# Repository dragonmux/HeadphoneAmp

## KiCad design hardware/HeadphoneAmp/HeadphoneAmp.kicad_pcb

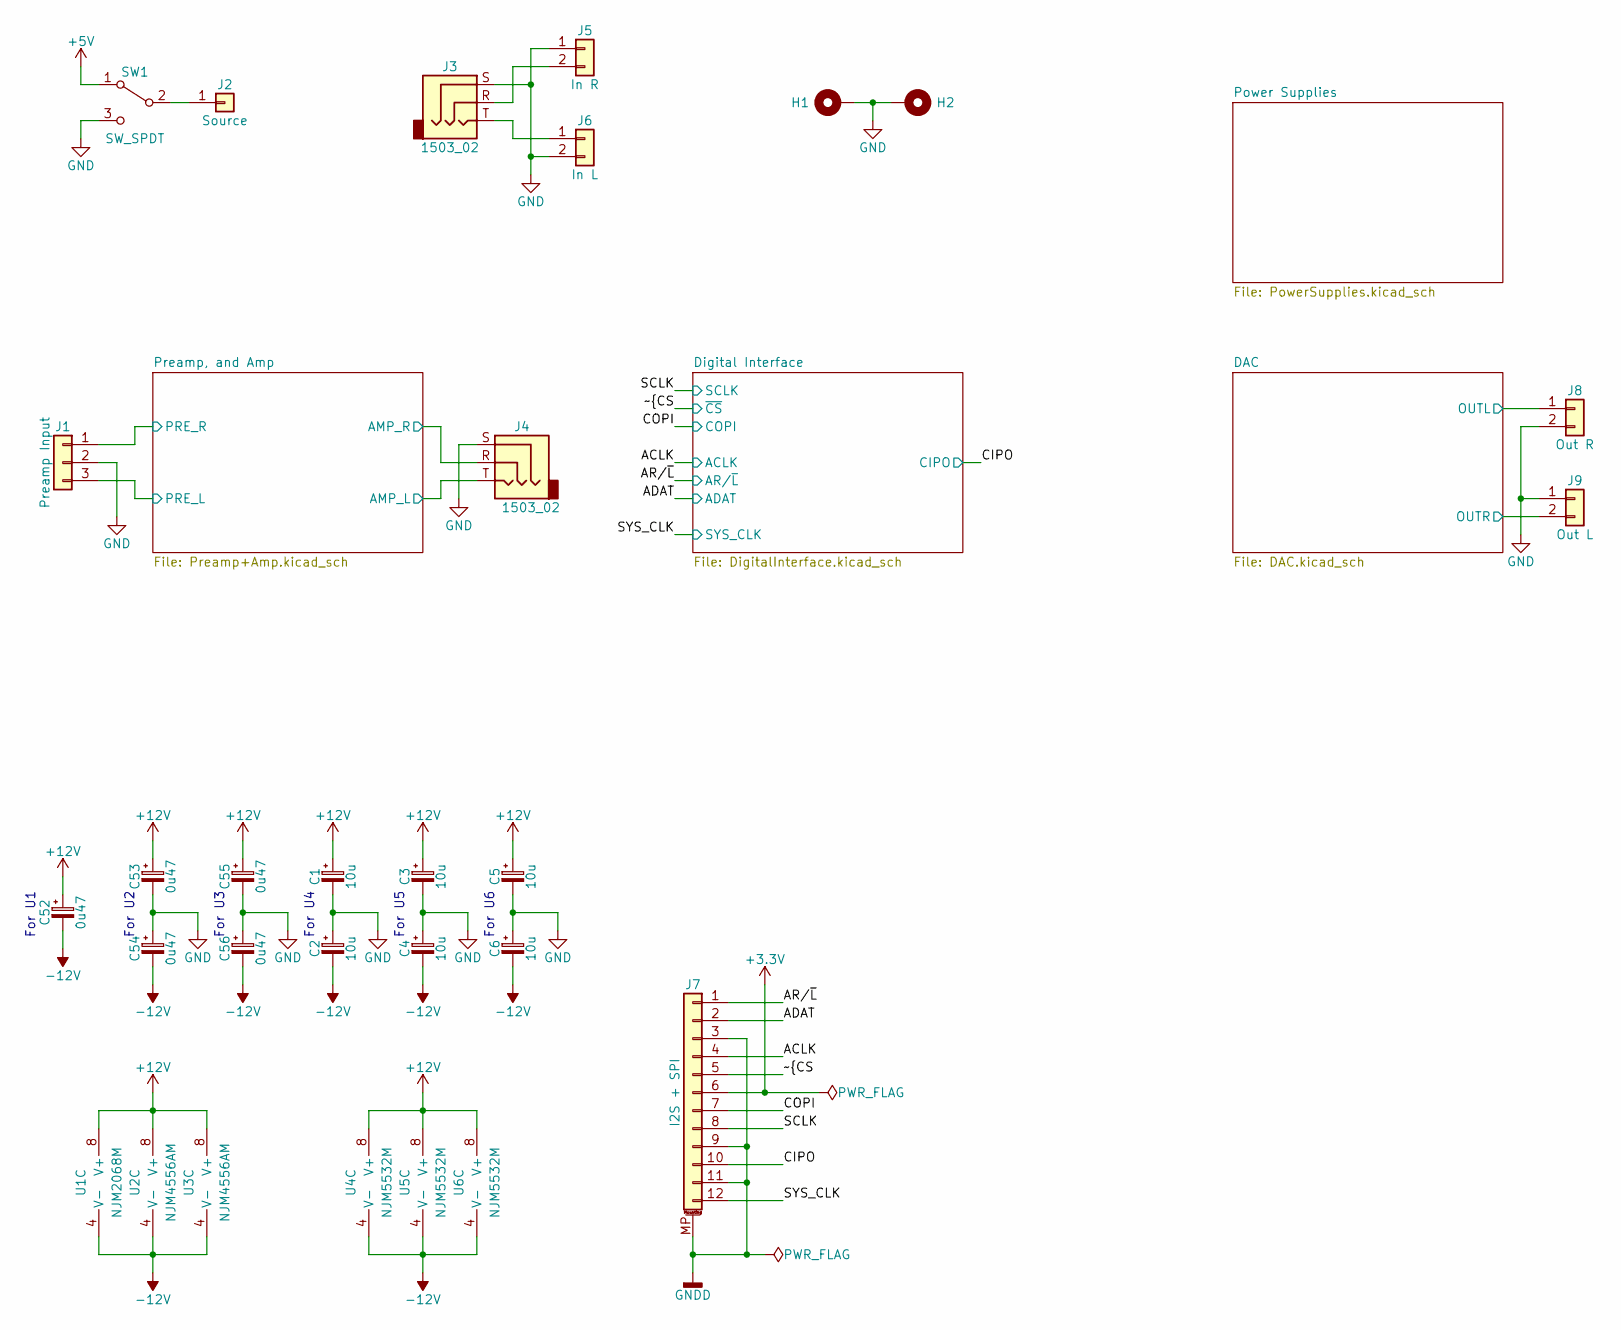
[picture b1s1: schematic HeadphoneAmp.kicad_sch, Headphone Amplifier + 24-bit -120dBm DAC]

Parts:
C1, C2, C3, C4, C5, C6: 10u; CP_EIA-3216-18_A; MPN 293D106X0016A2TE3
C52, C53, C54, C55, C56: 0u47; CP_EIA-3216-18_A; MPN F931V474KAA
H1, H2: MountingHole_Pad; MountingHole_3.2mm_M3_Pad
J1: Preamp Input; PinHeader_1x03_P2.54mm_Vertical
J2: Source; PinHeader_1x01_P2.54mm_Vertical
J3, J4: 1503_02; 1503-02; MPN 1503 02
J5: In R; PinHeader_1x02_P2.54mm_Vertical
J6: In L; PinHeader_1x02_P2.54mm_Vertical
J7: I2S + SPI; 1-17345952-2_1x12-1MP_P0.5mm_Horizontal; MPN 1-1734592-2
J8: Out R; PinHeader_1x02_P2.54mm_Vertical
J9: Out L; PinHeader_1x02_P2.54mm_Vertical
SW1: SW_SPDT; PN1x-30EQ; MPN PN12SHNA03QE
U1: NJM2068M; SO-8_5.3x5.3mm_P1.27mm; MPN NJM2068M
U2, U3: NJM4556AM; SO-8_5.3x5.3mm_P1.27mm; MPN NJM4556AM
U4, U5, U6: NJM5532M; SO-8_5.3x5.3mm_P1.27mm; MPN NJM5532M

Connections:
+3V3: J7.6; also elsewhere on the board
+5V: SW1.1 (A); also elsewhere on the board
+12V: C1.1, C3.1, C5.1, C52.1, C53.1, C55.1, U1.8 (V+), U2.8 (V+), U3.8 (V+), U4.8 (V+), U5.8 (V+), U6.8 (V+); also elsewhere on the board
-12V: C2.2, C4.2, C6.2, C52.2, C54.2, C56.2, U1.4 (V-), U2.4 (V-), U3.4 (V-), U4.4 (V-), U5.4 (V-), U6.4 (V-); also elsewhere on the board
/ACLK: J7.4; also elsewhere on the board
/ADAT: J7.2; also elsewhere on the board
/AR/~L: J7.1; also elsewhere on the board
/CIPO: J7.10; also elsewhere on the board
/COPI: J7.7; also elsewhere on the board
/DAC/OUTL: J8.1; also elsewhere on the board
/DAC/OUTR: J9.2; also elsewhere on the board
/Preamp, and Amp/AMP_L: J4.T; also elsewhere on the board
/Preamp, and Amp/AMP_R: J4.R; also elsewhere on the board
/Preamp, and Amp/PRE_L: J1.3; also elsewhere on the board
/Preamp, and Amp/PRE_R: J1.1; also elsewhere on the board
/SCLK: J7.8; also elsewhere on the board
/SYS_CLK: J7.12; also elsewhere on the board
/~CS: J7.5; also elsewhere on the board
GND: C1.2, C2.1, C3.2, C4.1, C5.2, C6.1, C53.2, C54.1, C55.2, C56.1, H1.1, H2.1, J1.2, J3.S, J4.S, J5.1, J6.2, J8.2, J9.1, SW1.3 (C); also elsewhere on the board
GNDD: J7.3, J7.9, J7.11, J7.MP (MountPin); also elsewhere on the board
unnamed: J2.1, SW1.2 (B)
unnamed: J3.R, J5.2
unnamed: J3.T, J6.1

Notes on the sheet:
For U4
For U6
For U3
For U1
For U5
For U2

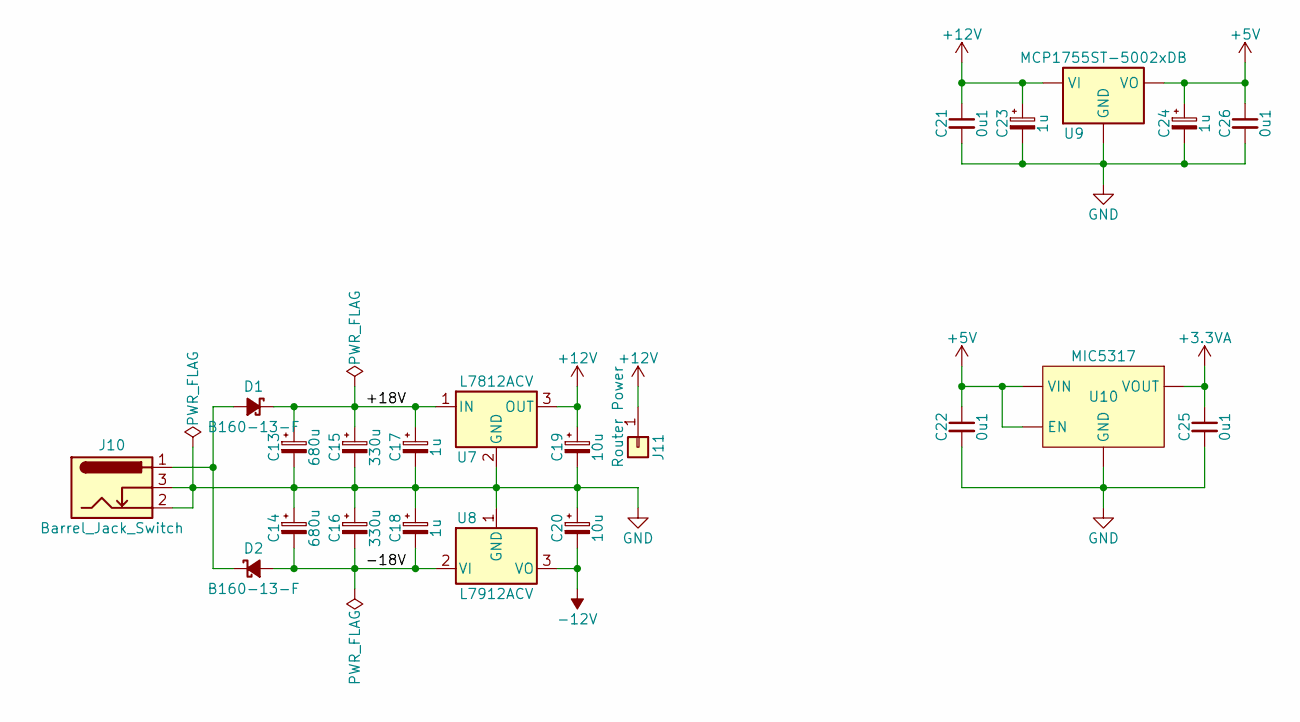
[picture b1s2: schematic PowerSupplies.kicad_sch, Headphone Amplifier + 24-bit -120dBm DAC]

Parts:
C13, C14: 680u; CP_Radial_D10.0mm_P5.00mm; MPN 25PX680MEFC10X12.5
C15, C16: 330u; CP_Radial_D8.0mm_P3.50mm; MPN 25PX330MEFC8X11.5
C17, C18: 1u; CP_EIA-3216-18_A; MPN 293D105X9025A2TE3
C19, C20: 10u; CP_EIA-3216-18_A; MPN 293D106X0016A2TE3
C21, C22, C26: 0u1; C1210; MPN ECH-U1C104GX5
C23, C24: 1u; CP_EIA-3216-18_A; MPN 293D105X9016A2TE3
C25: 0u1; C0603; MPN CGA3E2X7R1E104K080AA
D1, D2: B160-13-F; D_SMA; MPN B160-13-F
J10: Barrel_Jack_Switch; BarrelJack_GCT_DCJ200-10-A_Horizontal; MPN DCJ200-10-A-K1-K
J11: Router Power; PinHeader_1x01_P2.54mm_Vertical
U7: L7812ACV; TO-220-3_Vertical; MPN L7812ACV
U8: L7912ACV; TO-220-3_Vertical; MPN L7912ACV
U9: MCP1755ST-5002xDB; SOT-223; MPN MCP1755ST-5002E/DB
U10: MIC5317; SOT-23-5; MPN MIC5317-3.3YM5-TR

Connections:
+3.3VA: C25.1, U10.5 (VOUT); also elsewhere on the board
+5V: C22.1, C24.1, C26.1, U9.3 (VO), U10.1 (VIN), U10.3 (EN); also elsewhere on the board
+12V: C19.1, C21.1, C23.1, J11.1, U7.3 (OUT), U9.1 (VI); also elsewhere on the board
-12V: C20.2, U8.3 (VO); also elsewhere on the board
/Power Supplies/+18V: C13.1, C15.1, C17.1, D1.1 (K), U7.1 (IN)
/Power Supplies/-18V: C14.2, C16.2, C18.2, D2.2 (A), U8.2 (VI)
GND: C13.2, C14.1, C15.2, C16.1, C17.2, C18.1, C19.2, C20.1, C21.2, C22.2, C23.2, C24.2, C25.2, C26.2, J10.2, J10.3, U7.2 (GND), U8.1 (GND), U9.2 (GND), U10.2 (GND); also elsewhere on the board
unnamed: D1.2 (A), D2.1 (K), J10.1

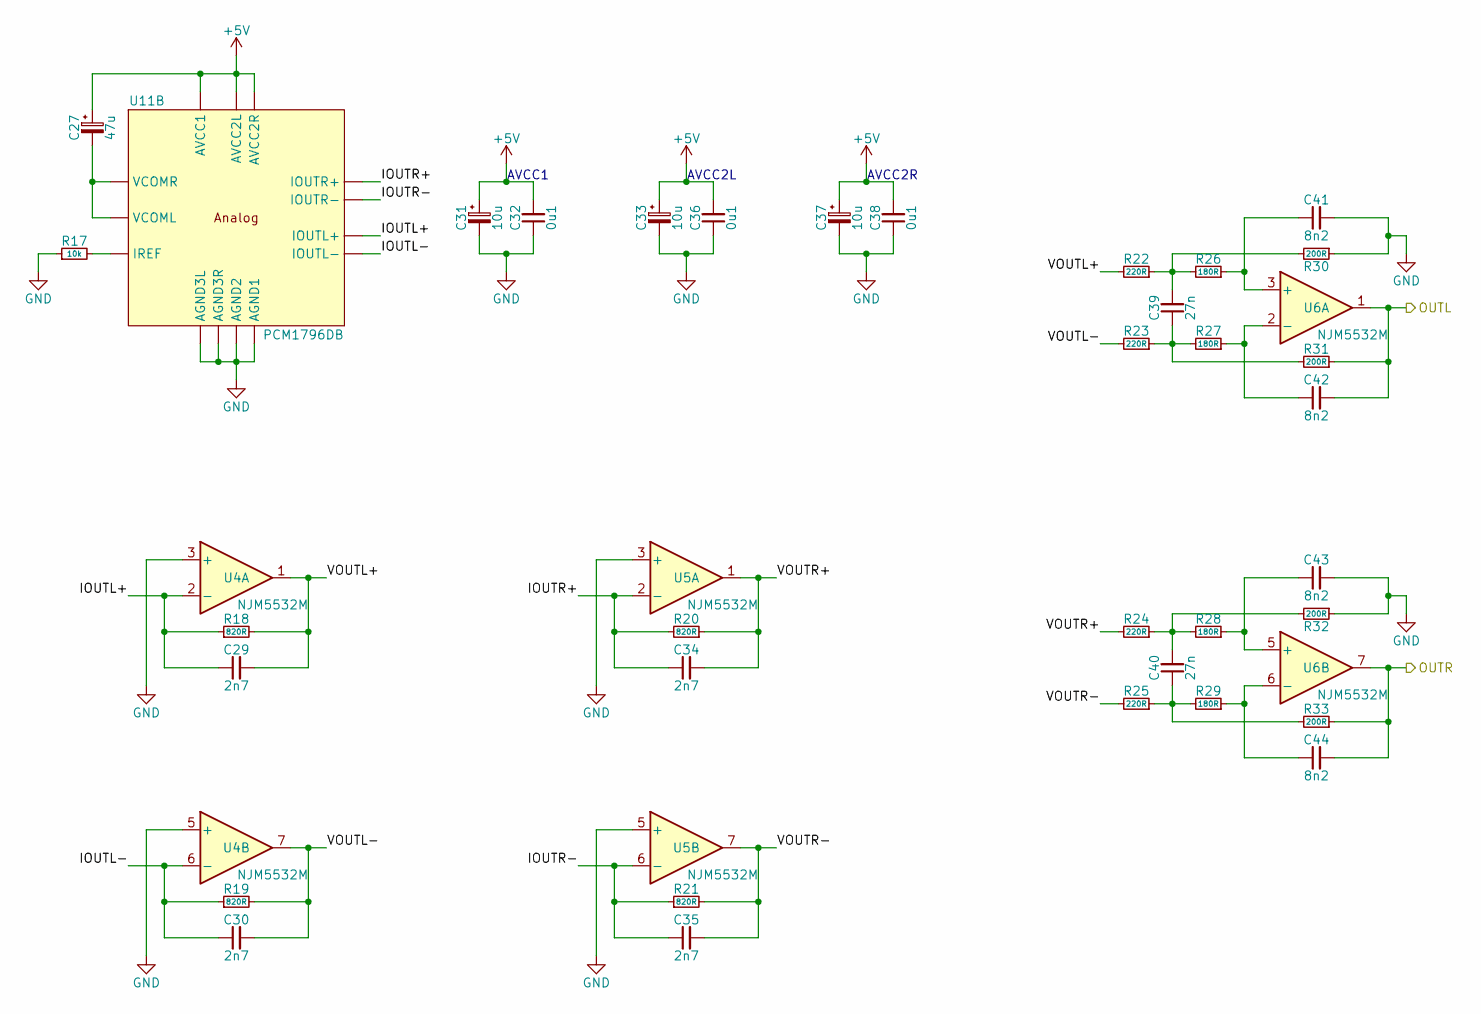
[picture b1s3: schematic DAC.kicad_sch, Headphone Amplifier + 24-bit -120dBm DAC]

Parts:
C27: 47u; CP_EIA-3528-21_B; MPN 293D476X9010B2TE3
C29, C30, C34, C35: 2n7; C0603; MPN ECH-U1C272GX5
C31, C33, C37: 10u; CP_EIA-3216-18_A; MPN 293D106X0016A2TE3
C32, C36, C38: 0u1; C1210; MPN ECH-U1C104GX5
C39, C40: 27n; C1206; MPN ECH-U1C273GX5
C41, C42, C43, C44: 8n2; C0805; MPN ECH-U1C822GX5
R17: 10k; R0603; MPN RN73H1JTTD1002B25
R18, R19, R20, R21: 820R; R0603; MPN RN73H1JTTD8200F100
R22, R23, R24, R25: 220R; R0603; MPN RN73H1JTTD2200F100
R26, R27, R28, R29: 180R; R0603; MPN RN73H1JTTD1800F100
R30, R31, R32, R33: 200R; R0603; MPN RN73H1JTTD2000B25
U4, U5, U6: NJM5532M; SO-8_5.3x5.3mm_P1.27mm; MPN NJM5532M
U11: PCM1796DB; SSOP-28_5.3x10.2mm_P0.65mm; MPN PCM1796DB

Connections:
+5V: C27.1, C31.1, C32.2, C33.1, C36.2, C37.1, C38.2, U11.15 (AVCC2R), U11.23 (AVCC1), U11.28 (AVCC2L); also elsewhere on the board
/DAC/IOUTL+: C29.1, R18.1, U4.2 (-), U11.25 (IOUTL+)
/DAC/IOUTL-: C30.1, R19.1, U4.6 (-), U11.26 (IOUTL-)
/DAC/IOUTR+: C34.1, R20.2, U5.2 (-), U11.17 (IOUTR+)
/DAC/IOUTR-: C35.1, R21.1, U5.6 (-), U11.18 (IOUTR-)
/DAC/OUTL: C42.2, R31.1, U6.1; also elsewhere on the board
/DAC/OUTR: C44.2, R33.1, U6.7; also elsewhere on the board
/DAC/VOUTL+: C29.2, R18.2, R22.2, U4.1
/DAC/VOUTL-: C30.2, R19.2, R23.2, U4.7
/DAC/VOUTR+: C34.2, R20.1, R24.2, U5.1
/DAC/VOUTR-: C35.2, R21.2, R25.2, U5.7
GND: C31.2, C32.1, C33.2, C36.1, C37.2, C38.1, C41.2, C43.2, R17.1, R30.1, R32.1, U4.3 (+), U4.5 (+), U5.3 (+), U5.5 (+), U11.16 (AGND3R), U11.19 (AGND1), U11.24 (AGND2), U11.27 (AGND3L); also elsewhere on the board
unnamed: C27.2, U11.21 (VCOMR), U11.22 (VCOML)
unnamed: C39.1, R23.1, R27.2, R31.2
unnamed: C39.2, R22.1, R26.2, R30.2
unnamed: C40.1, R25.1, R29.2, R33.2
unnamed: C40.2, R24.1, R28.2, R32.2
unnamed: C41.1, R26.1, U6.3 (+)
unnamed: C42.1, R27.1, U6.2 (-)
unnamed: C43.1, R28.1, U6.5 (+)
unnamed: C44.1, R29.1, U6.6 (-)
unnamed: R17.2, U11.20 (IREF)

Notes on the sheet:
AVCC2R
AVCC1
AVCC2L

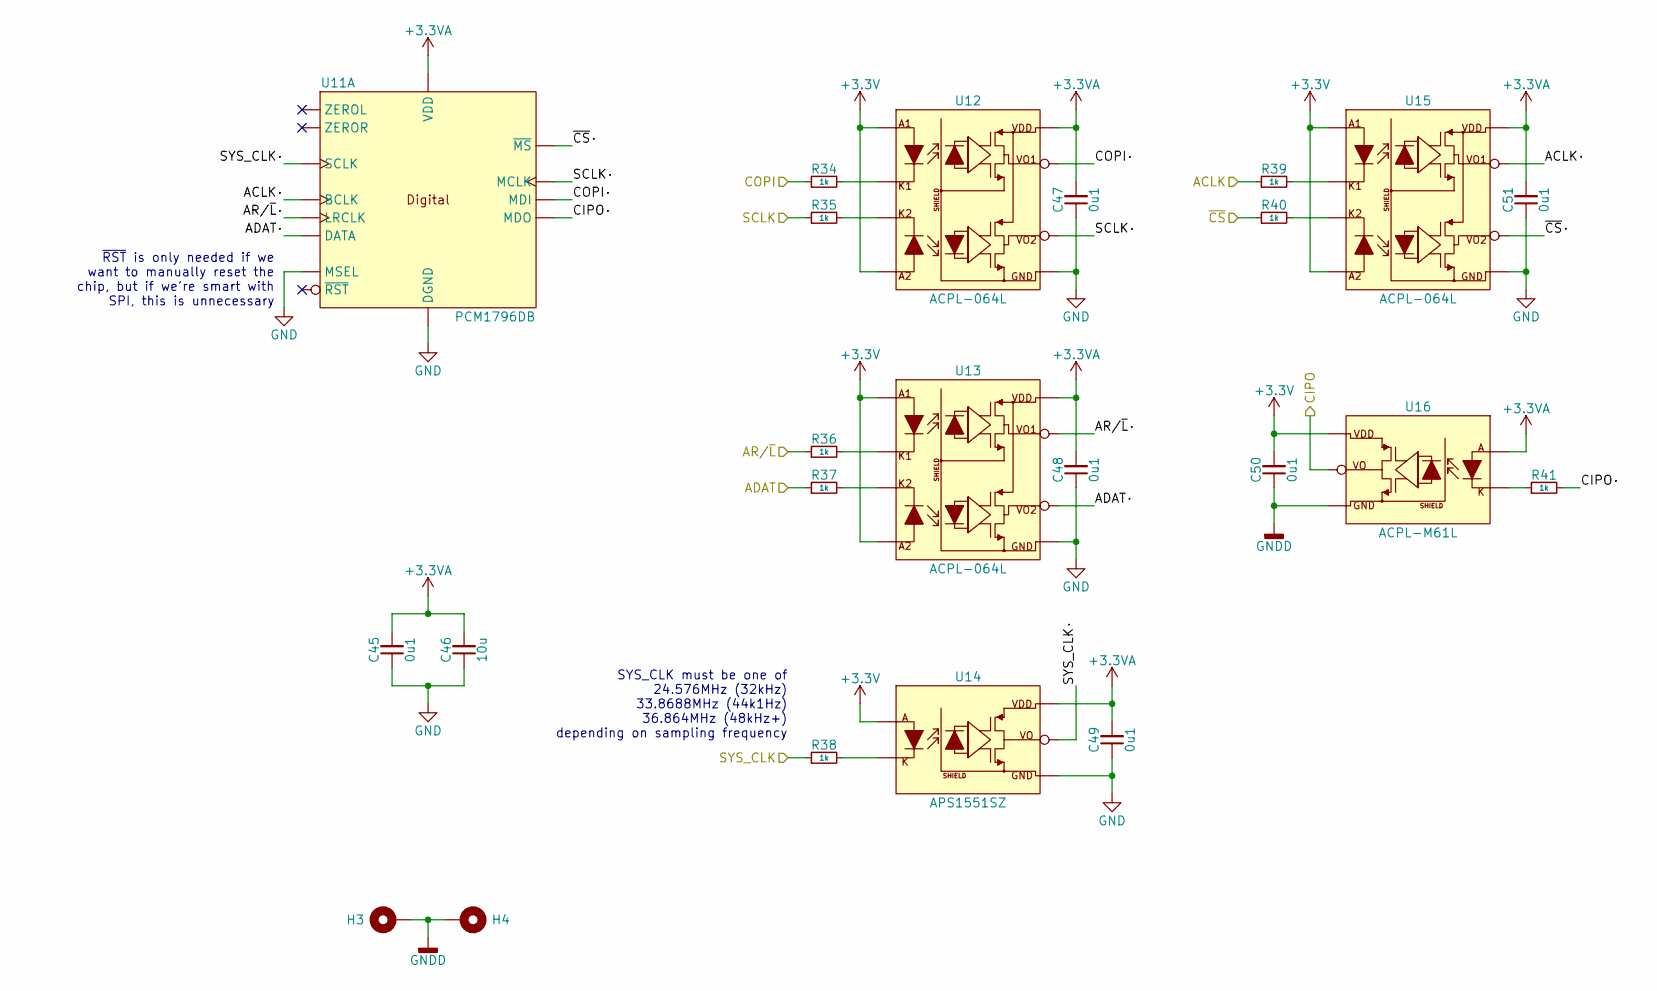
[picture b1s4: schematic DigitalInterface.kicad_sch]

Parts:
C45, C47, C48, C49, C50, C51: 0u1; C0603; MPN CGA3E2X7R1E104K080AA
C46: 10u; C0805; MPN GRM21BR61E106KA73L
H3, H4: MountingHole_Pad; MountingHole_3.2mm_M3_Pad
R34, R35, R36, R37, R38, R39, R40, R41: 1k; R0603; MPN CRCW06031K00FKEA
U11: PCM1796DB; SSOP-28_5.3x10.2mm_P0.65mm; MPN PCM1796DB
U12, U13, U15: ACPL-064L; SO-8_3.9x4.9mm_P1.27mm; MPN ACPL-064L-500E
U14: APS1551SZ; SO-5_4.4x4.3mm_P1.27mm; MPN APS1551SZ
U16: ACPL-M61L; SO-5_4.4x3.6mm_P1.27mm; MPN ACPL-M61L-5x0E

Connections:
+3.3VA: C45.2, C46.2, C47.2, C48.2, C49.2, C51.2, U11.9 (VDD), U12.8 (VDD), U13.8 (VDD), U14.6 (VDD), U15.8 (VDD), U16.1 (A); also elsewhere on the board
+3V3: C50.2, U12.1 (A1), U12.4 (A2), U13.1 (A1), U13.4 (A2), U14.1 (A), U15.1 (A1), U15.4 (A2), U16.6 (VDD); also elsewhere on the board
/ACLK: R39.1; also elsewhere on the board
/ADAT: R37.1; also elsewhere on the board
/AR/~L: R36.1; also elsewhere on the board
/CIPO: U16.5 (VO); also elsewhere on the board
/COPI: R34.1; also elsewhere on the board
/Digital Interface/ACLK·: U11.6 (BCLK), U15.7 (VO1)
/Digital Interface/ADAT·: U11.5 (DATA), U13.6 (VO2)
/Digital Interface/AR/~L·: U11.4 (LRCLK), U13.7 (VO1)
/Digital Interface/CIPO·: R41.2, U11.13 (MDO)
/Digital Interface/COPI·: U11.11 (MDI), U12.7 (VO1)
/Digital Interface/SCLK·: U11.12 (MCLK), U12.6 (VO2)
/Digital Interface/SYS_CLK·: U11.7 (SCLK), U14.5 (VO)
/Digital Interface/~CS·: U11.10 (~MS), U15.6 (VO2)
/SCLK: R35.1; also elsewhere on the board
/SYS_CLK: R38.1; also elsewhere on the board
/~CS: R40.1; also elsewhere on the board
GND: C45.1, C46.1, C47.1, C48.1, C49.1, C51.1, U11.3 (MSEL), U11.8 (DGND), U12.5 (GND), U13.5 (GND), U14.4 (GND), U15.5 (GND); also elsewhere on the board
GNDD: C50.1, H3.1, H4.1, U16.4 (GND); also elsewhere on the board
unnamed: R34.2, U12.2 (K1)
unnamed: R35.2, U12.3 (K2)
unnamed: R36.2, U13.2 (K1)
unnamed: R37.2, U13.3 (K2)
unnamed: R38.2, U14.3 (K)
unnamed: R39.2, U15.2 (K1)
unnamed: R40.2, U15.3 (K2)
unnamed: R41.1, U16.3 (K)

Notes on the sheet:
SYS_CLK must be one of 24.576MHz (32kHz) 33.8688MHz (44k1Hz) 36.864MHz (48kHz+) depending on sampling frequency
~{RST} is only needed if we want to manually reset the chip, but if we're smart with SPI, this is unnecessary

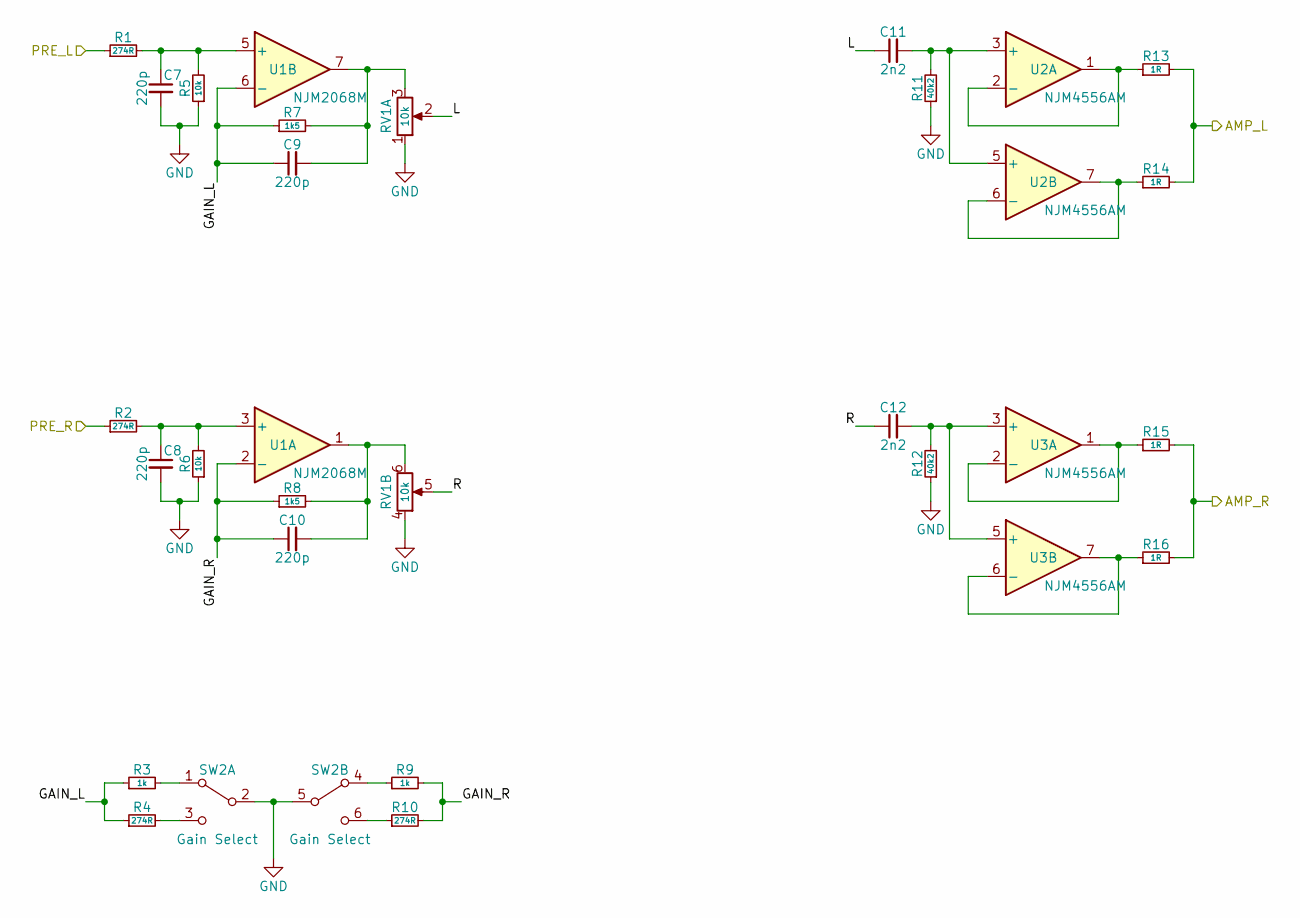
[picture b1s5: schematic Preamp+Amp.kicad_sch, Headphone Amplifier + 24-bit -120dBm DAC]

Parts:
C7, C8, C9, C10: 220p; C0603; MPN ECH-U1C221GX5
C11, C12: 2n2; C0603; MPN ECH-U1C222GX5
R1, R2, R4, R10: 274R; R0603; MPN RN731JTTD2740B25
R3, R9: 1k; R0603; MPN RN73H1JTTD1001D25
R5, R6: 10k; R0603; MPN RN73H1JTTD1002B25
R7, R8: 1k5; R0603; MPN RN73H1JTTD1501B25
R11, R12: 40k2; R0603; MPN RN73H1ETTP4022F25
R13, R14, R15, R16: 1R; R1206; MPN MCA12060C1008FP500
RV1: 10k; PTD902; MPN PTD902-2015F-A103
SW2: Gain Select; PN2x-30EQ; MPN PN22LENA03QE
U1: NJM2068M; SO-8_5.3x5.3mm_P1.27mm; MPN NJM2068M
U2, U3: NJM4556AM; SO-8_5.3x5.3mm_P1.27mm; MPN NJM4556AM

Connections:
/Preamp, and Amp/AMP_L: R13.2, R14.2; also elsewhere on the board
/Preamp, and Amp/AMP_R: R15.2, R16.2; also elsewhere on the board
/Preamp, and Amp/GAIN_L: C9.1, R3.1, R4.1, R7.1, U1.6 (-)
/Preamp, and Amp/GAIN_R: C10.1, R8.1, R9.2, R10.2, U1.2 (-)
/Preamp, and Amp/L: C11.1, RV1.2
/Preamp, and Amp/PRE_L: R1.1; also elsewhere on the board
/Preamp, and Amp/PRE_R: R2.1; also elsewhere on the board
/Preamp, and Amp/R: C12.1, RV1.5
GND: C7.2, C8.2, R5.1, R6.1, R11.1, R12.1, RV1.1, RV1.4, SW2.2 (B), SW2.5 (B); also elsewhere on the board
unnamed: C7.1, R1.2, R5.2, U1.5 (+)
unnamed: C8.1, R2.2, R6.2, U1.3 (+)
unnamed: C9.2, R7.2, RV1.3, U1.7
unnamed: C10.2, R8.2, RV1.6, U1.1
unnamed: C11.2, R11.2, U2.3 (+), U2.5 (+)
unnamed: C12.2, R12.2, U3.3 (+), U3.5 (+)
unnamed: R3.2, SW2.1 (A)
unnamed: R4.2, SW2.3 (C)
unnamed: R9.1, SW2.4 (A)
unnamed: R10.1, SW2.6 (C)
unnamed: R13.1, U2.1, U2.2 (-)
unnamed: R14.1, U2.6 (-), U2.7
unnamed: R15.1, U3.1, U3.2 (-)
unnamed: R16.1, U3.6 (-), U3.7

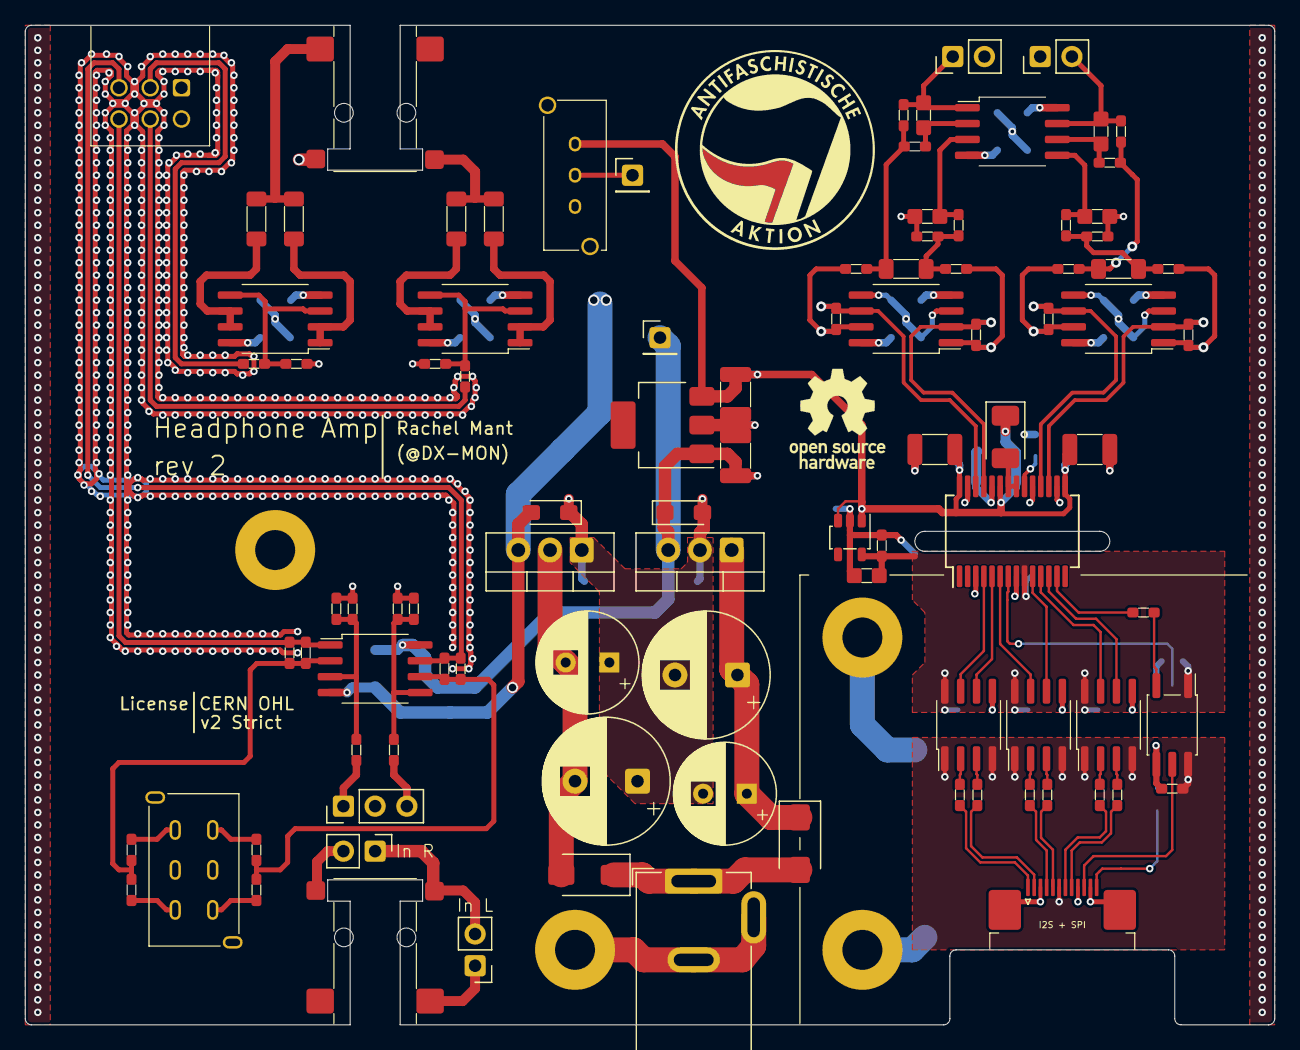
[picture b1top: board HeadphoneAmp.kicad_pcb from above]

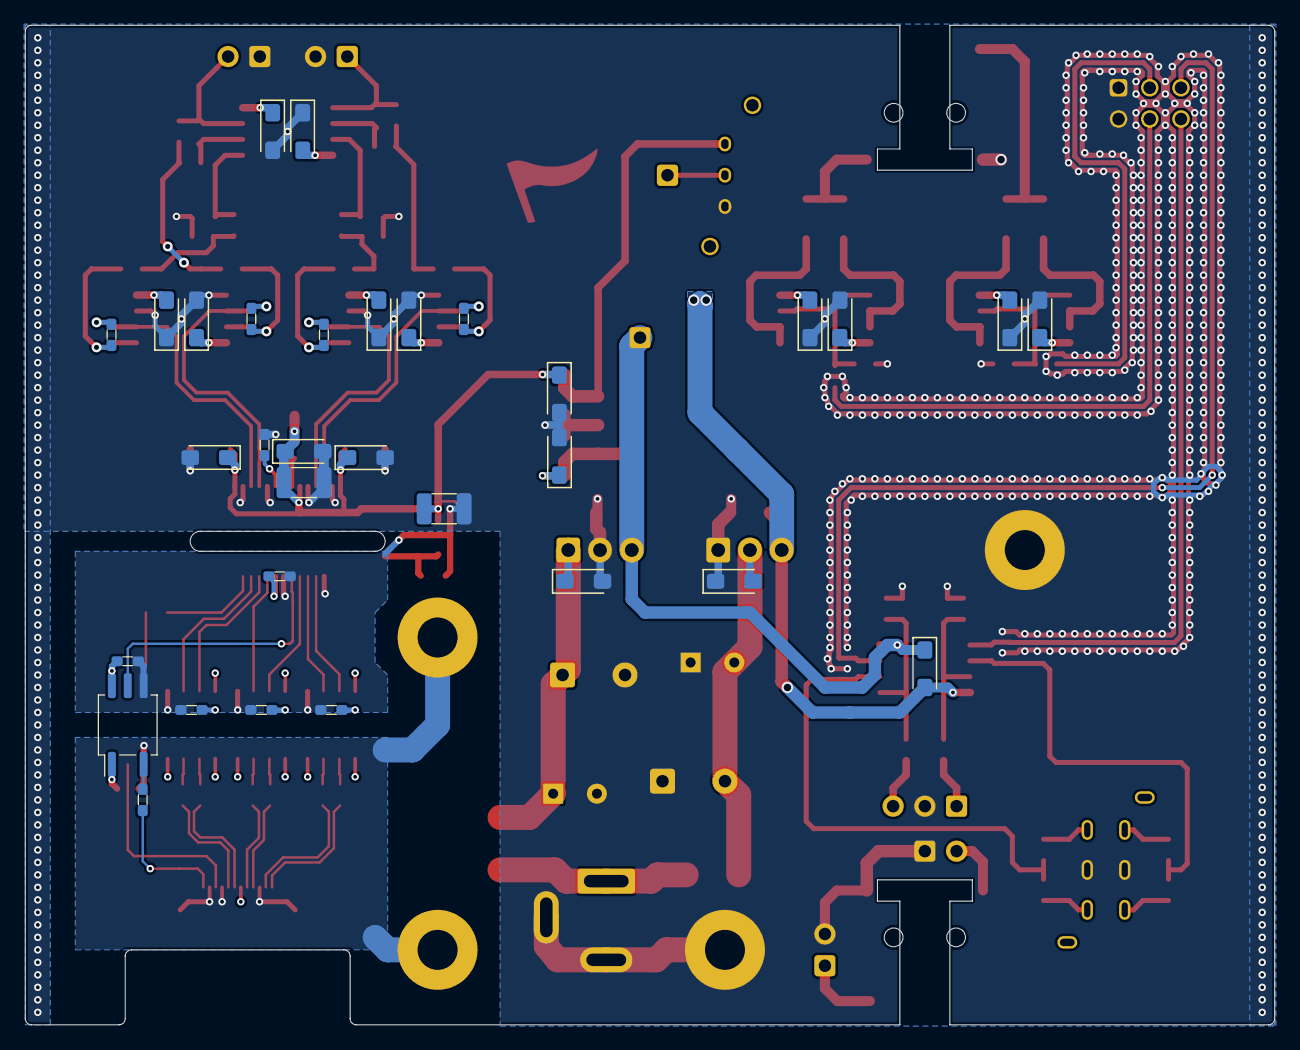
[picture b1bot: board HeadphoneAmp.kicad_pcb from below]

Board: 4 copper layers, 100.0 x 80.0 mm, 134 parts (32 on the bottom side), 79 nets.

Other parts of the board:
G1: ANTIFA; Antifaschistische-Aktion_Inv_600dpi
G2: OSHW-Logo_7.5x8mm_SilkScreen

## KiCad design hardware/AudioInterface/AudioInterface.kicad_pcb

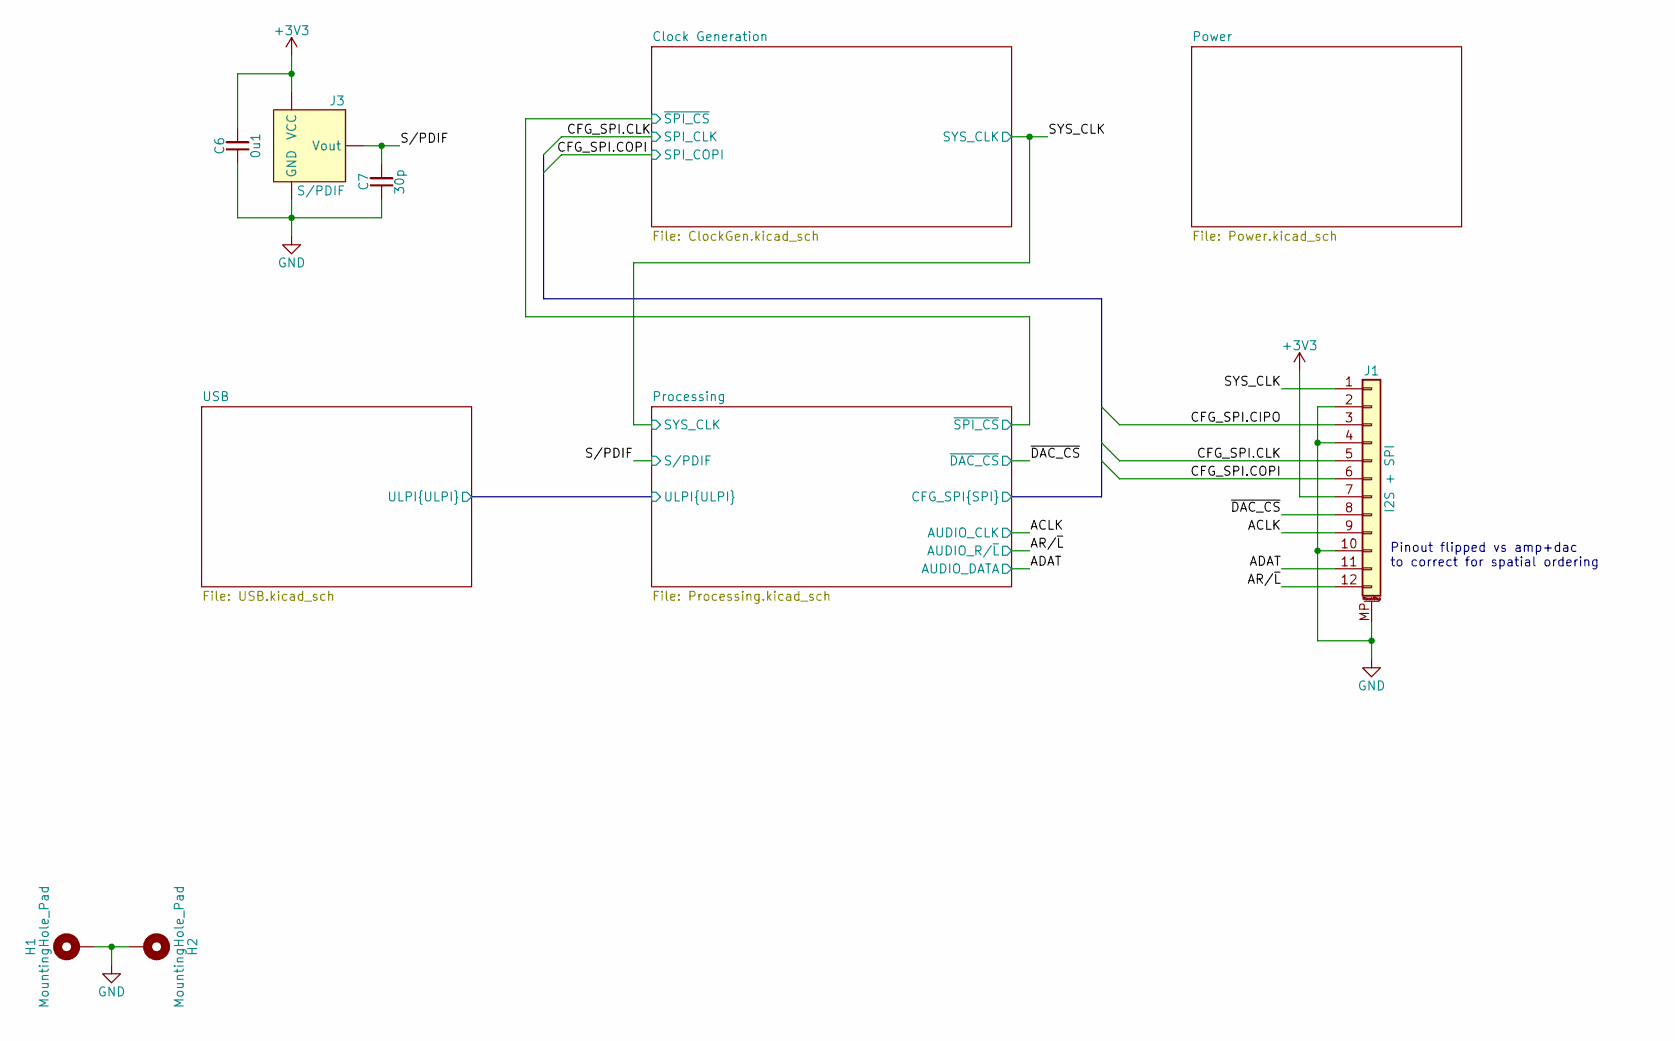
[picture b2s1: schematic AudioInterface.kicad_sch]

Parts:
C6: 0u1; C0603; MPN CGA3E2X7R1E104K080AA
C7: 30p; C0603; MPN CC0603FRNPO9BN300
H1, H2: MountingHole_Pad; MountingHole_3.2mm_M3_Pad
J1: I2S + SPI; 1-17345952-2_1x12-1MP_P0.5mm_Horizontal; MPN 1-1734592-2
J3: S/PDIF; S-PDIF_Receiver; MPN FCR684208R

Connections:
+3V3: C6.2, J1.7, J3.3 (VCC); also elsewhere on the board
/ACLK: J1.9; also elsewhere on the board
/ADAT: J1.11; also elsewhere on the board
/AR/~L: J1.12; also elsewhere on the board
/Processing/CFG_SPI.CIPO: J1.3; also elsewhere on the board
/Processing/CFG_SPI.CLK: J1.5; also elsewhere on the board
/Processing/CFG_SPI.COPI: J1.6; also elsewhere on the board
/SYS_CLK: J1.1; also elsewhere on the board
/S/PDIF: C7.2, J3.1 (Vout); also elsewhere on the board
/~DAC_CS: J1.8; also elsewhere on the board
DGND: C6.1, C7.1, H1.1, H2.1, J1.2, J1.4, J1.10, J1.MP (MountPin), J3.2 (GND); also elsewhere on the board

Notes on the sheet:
Pinout flipped vs amp+dac to correct for spatial ordering

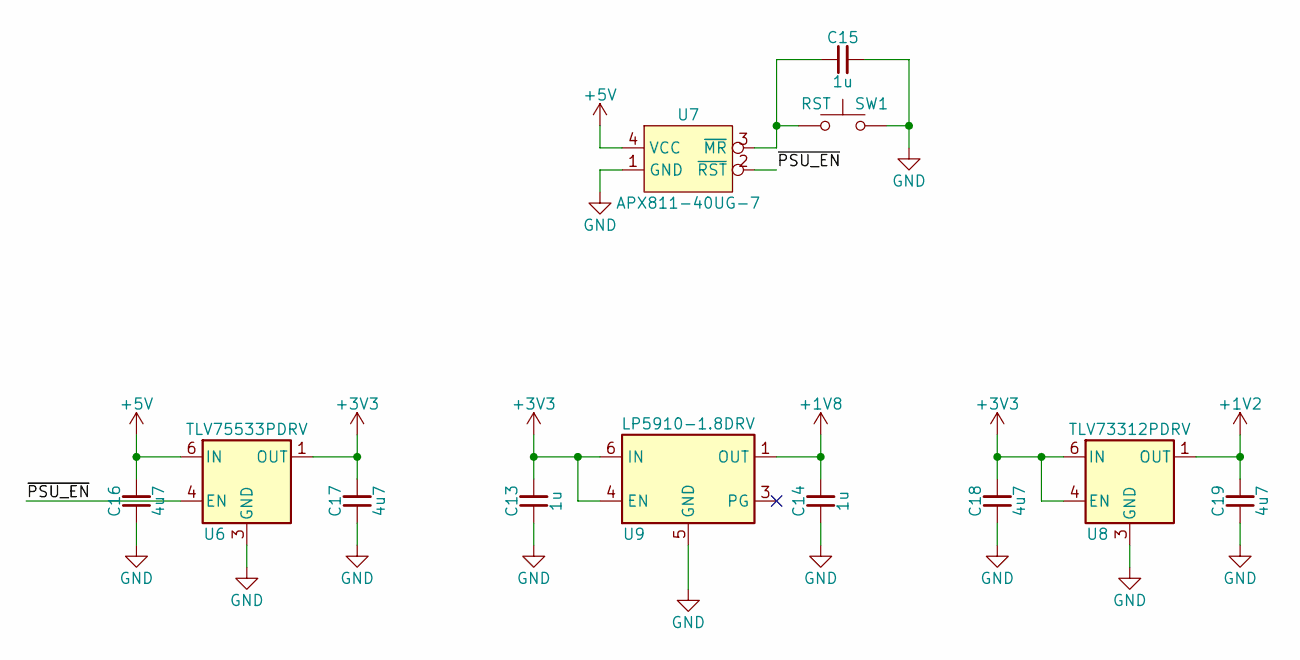
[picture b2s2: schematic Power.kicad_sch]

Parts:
C13, C14, C15: 1u; C0603; MPN C0603C105K4RAC7867
C16, C17, C18, C19: 4u7; C0603; MPN C1608X5R1C475K080AC
SW1: RST; B3U-1000P-B; MPN B3U-1000P-B
U6: TLV75533PDRV; WSON-6-1EP_2x2mm_P0.65mm_EP1x1.6mm; MPN TLV75533PDRVR
U7: APX811-40UG-7; SOT-143; MPN APX811-40UG-7
U8: TLV73312PDRV; WSON-6-1EP_2x2mm_P0.65mm_EP1x1.6mm; MPN TLV73312PQDRVRQ1
U9: LP5910-1.8DRV; WSON-6-1EP_2x2mm_P0.65mm_EP1x1.6mm; MPN LP5910-1.8DRVR

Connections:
+1V2: C19.2, U8.1 (OUT); also elsewhere on the board
+1V8: C14.2, U9.1 (OUT); also elsewhere on the board
+3V3: C13.2, C17.2, C18.2, U6.1 (OUT), U8.4 (EN), U8.6 (IN), U9.4 (EN), U9.6 (IN); also elsewhere on the board
+5V: C16.2, U6.6 (IN), U7.4 (VCC); also elsewhere on the board
/Power/~PSU_EN: U6.4 (EN), U7.2 (~RST)
DGND: C13.1, C14.1, C15.2, C16.1, C17.1, C18.1, C19.1, SW1.2, U6.2 (NC), U6.3 (GND), U6.5 (NC), U6.7 (GND), U7.1 (GND), U8.2 (NC), U8.3 (GND), U8.5 (NC), U8.7 (GND), U9.2 (NC), U9.5 (GND), U9.7 (EP); also elsewhere on the board
unnamed: C15.1, SW1.1, U7.3 (~MR)

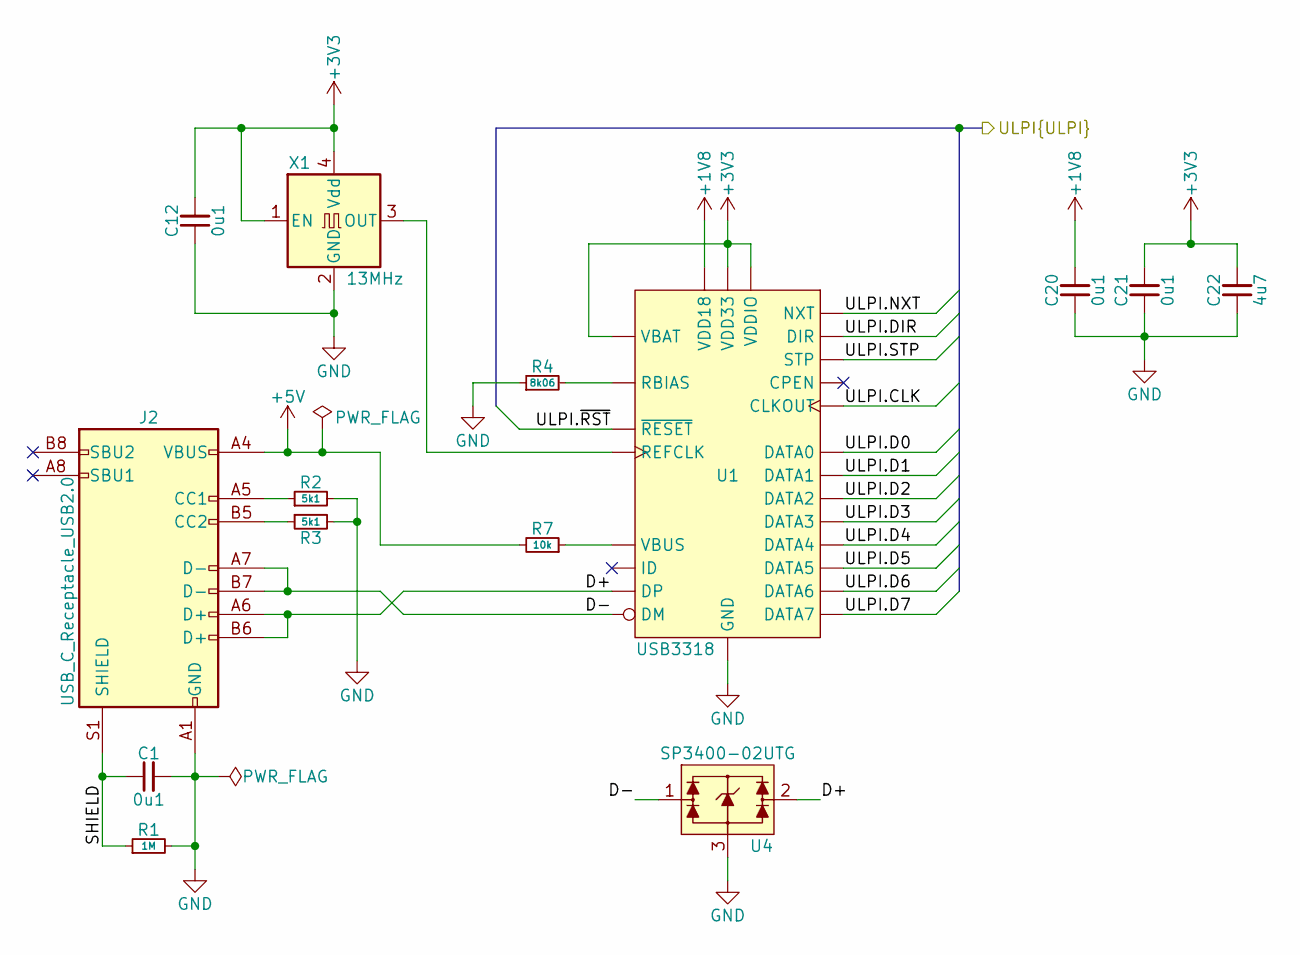
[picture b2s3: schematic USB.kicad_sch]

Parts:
C1, C12, C20, C21: 0u1; C0603; MPN CGA3E2X7R1E104K080AA
C22: 4u7; C0603; MPN C1608X5R1C475K080AC
J2: USB_C_Receptacle_USB2.0; USB_C_Receptacle_HRO_TYPE-C-31-M-12; MPN TYPE-C-31-M-12
R1: 1M; R0603; MPN CRCW06031M00FKEA
R2, R3: 5k1; R0603; MPN CRCW06035K10FKEA
R4: 8k06; R0603; MPN CRCW06038K06FKEA
R7: 10k; R0603; MPN CRCW060310K0FKEA
U1: USB3318; QFN-24-1EP_4x4mm_P0.5mm_EP2.6x2.6mm; MPN USB3318-CP-TR
U4: SP3400-02UTG; UDFN-6L; MPN SP3400-02UTG
X1: 13MHz; SMD2520; MPN 8W-13.000MBE-T

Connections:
+1V8: C20.2, U1.21 (VDD18); also elsewhere on the board
+3V3: C12.2, C21.2, C22.2, U1.3 (VBAT), U1.4 (VDD33), U1.17 (VDDIO), X1.1 (EN), X1.4 (Vdd); also elsewhere on the board
+5V: J2.A4 (VBUS), J2.A9 (VBUS), J2.B4 (VBUS), J2.B9 (VBUS), R7.2; also elsewhere on the board
/Processing/ULPI.CLK: U1.12 (CLKOUT); also elsewhere on the board
/Processing/ULPI.D0: U1.16 (DATA0); also elsewhere on the board
/Processing/ULPI.D1: U1.15 (DATA1); also elsewhere on the board
/Processing/ULPI.D2: U1.14 (DATA2); also elsewhere on the board
/Processing/ULPI.D3: U1.13 (DATA3); also elsewhere on the board
/Processing/ULPI.D4: U1.11 (DATA4); also elsewhere on the board
/Processing/ULPI.D5: U1.10 (DATA5); also elsewhere on the board
/Processing/ULPI.D6: U1.9 (DATA6); also elsewhere on the board
/Processing/ULPI.D7: U1.8 (DATA7); also elsewhere on the board
/Processing/ULPI.DIR: U1.19 (DIR); also elsewhere on the board
/Processing/ULPI.NXT: U1.18 (NXT); also elsewhere on the board
/Processing/ULPI.STP: U1.20 (STP); also elsewhere on the board
/Processing/ULPI.~RST: U1.22 (~RESET); also elsewhere on the board
/USB/D+: J2.A6 (D+), J2.B6 (D+), U1.6 (DP), U4.2 (IO2), U4.5 (NC)
/USB/D-: J2.A7 (D-), J2.B7 (D-), U1.5 (DM), U4.1 (IO1), U4.6 (NC)
/USB/SHIELD: C1.1, J2.S1 (SHIELD), R1.1
DGND: C1.2, C12.1, C20.1, C21.1, C22.1, J2.A1 (GND), J2.A12 (GND), J2.B1 (GND), J2.B12 (GND), R1.2, R2.2, R3.2, R4.1, U1.25 (GND), U4.3 (GND), U4.4 (GND), X1.2 (GND); also elsewhere on the board
unnamed: J2.A5 (CC1), R2.1
unnamed: J2.B5 (CC2), R3.1
unnamed: R4.2, U1.24 (RBIAS)
unnamed: R7.1, U1.2 (VBUS)
unnamed: U1.23 (REFCLK), X1.3 (OUT)

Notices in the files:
hardware/AudioInterface/AudioInterface.kicad_pcb:
CERN OHL
hardware/SignalRouter/SignalRouter.kicad_pcb:
CERN OHL v2 Strict
